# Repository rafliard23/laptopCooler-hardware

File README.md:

# laptopCooler-hardware

Hardware component of my custom laptop cooler project.

Using 3Pins PC Fans and speed controlled using 555 Timer and N-FET, powered with 12V Adapter (Ampere selection based on fan amp rating).

© 2022 Muhammad Rafli Ardiansyah

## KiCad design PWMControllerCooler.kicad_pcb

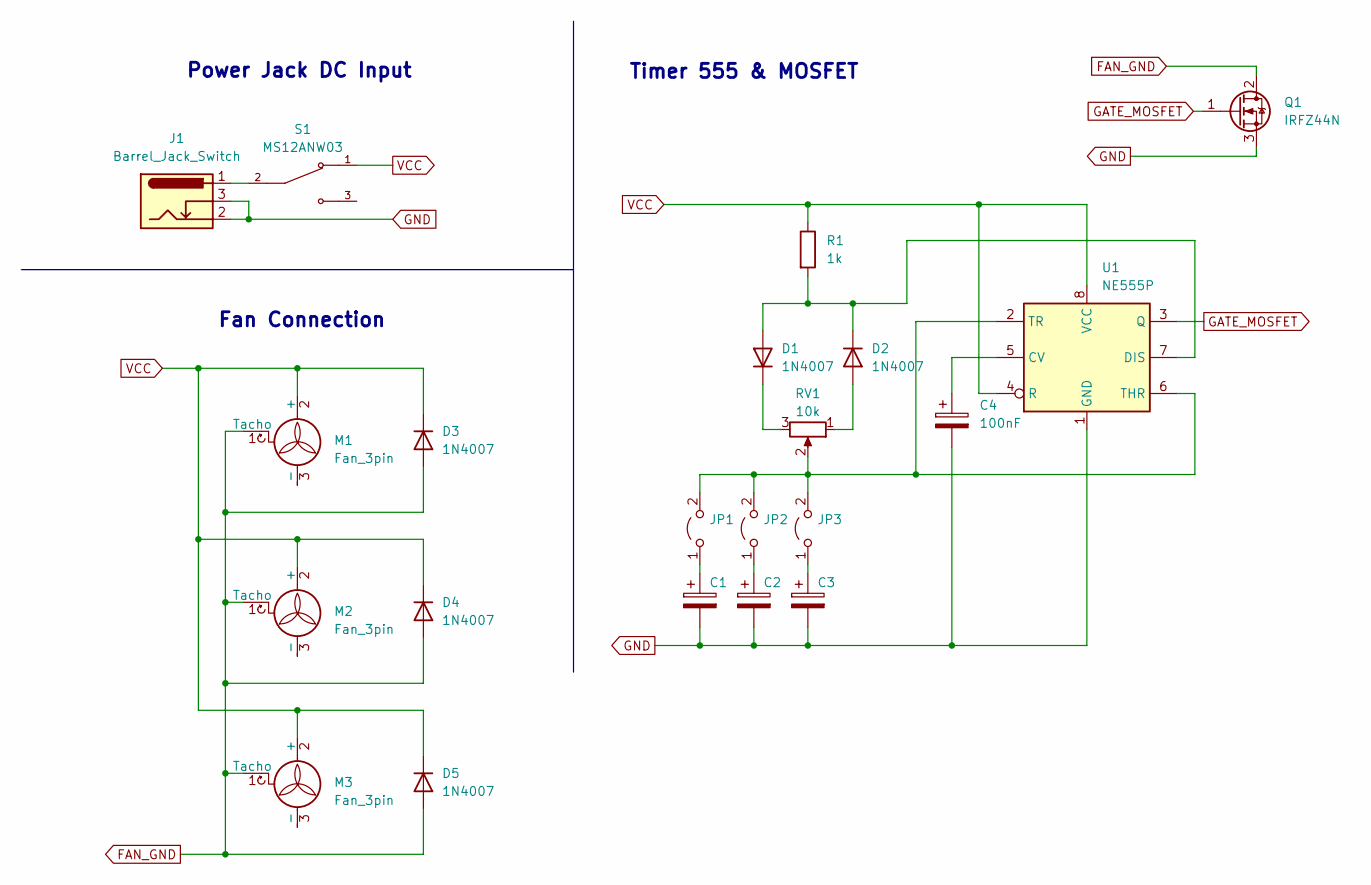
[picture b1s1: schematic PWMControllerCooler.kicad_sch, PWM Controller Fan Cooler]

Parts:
C1, C2, C3: C_Polarized; CP_Radial_D6.3mm_P2.50mm
C4: 100nF; CP_Radial_D8.0mm_P2.50mm
D1, D2, D3, D4, D5: 1N4007; D_DO-41_SOD81_P7.62mm_Horizontal
J1: Barrel_Jack_Switch; BarrelJack_Horizontal
JP1, JP2, JP3: Jumper_2_Open; PinHeader_1x02_P2.54mm_Vertical
M1, M2, M3: Fan_3pin; FanPinHeader_1x03_P2.54mm_Vertical
Q1: IRFZ44N; TO-220-3_Vertical
R1: 1k; R_Axial_DIN0207_L6.3mm_D2.5mm_P10.16mm_Horizontal
RV1: 10k; Potentiometer_Alps_RK163_Single_Horizontal
S1: MS12ANW03; SW_MS12ANW03
U1: NE555P; DIP-8_W7.62mm

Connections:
FAN_GND: D3.2 (A), D4.2 (A), D5.2 (A), M1.1 (Tacho), M2.1 (Tacho), M3.1 (Tacho), Q1.2 (D)
GATE_MOSFET: Q1.1 (G), U1.3 (Q)
GND: C1.2, C2.2, C3.2, C4.2, J1.2, J1.3, Q1.3 (S), U1.1 (GND)
unnamed: C1.1, JP1.1 (A)
unnamed: C2.1, JP2.1 (A)
unnamed: C3.1, JP3.1 (A)
unnamed: C4.1, U1.5 (CV)
unnamed: D1.1 (K), RV1.3
unnamed: D1.2 (A), D2.1 (K), R1.2, U1.7 (DIS)
unnamed: D2.2 (A), RV1.1
unnamed: JP1.2 (B), JP2.2 (B), JP3.2 (B), RV1.2, U1.2 (TR), U1.6 (THR)
unnamed: J1.1, S1.2
VCC: D3.1 (K), D4.1 (K), D5.1 (K), M1.2 (+), M2.2 (+), M3.2 (+), R1.1, S1.1, U1.4 (R), U1.8 (VCC)

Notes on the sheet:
Power Jack DC Input
Timer 555 & MOSFET
Fan Connection

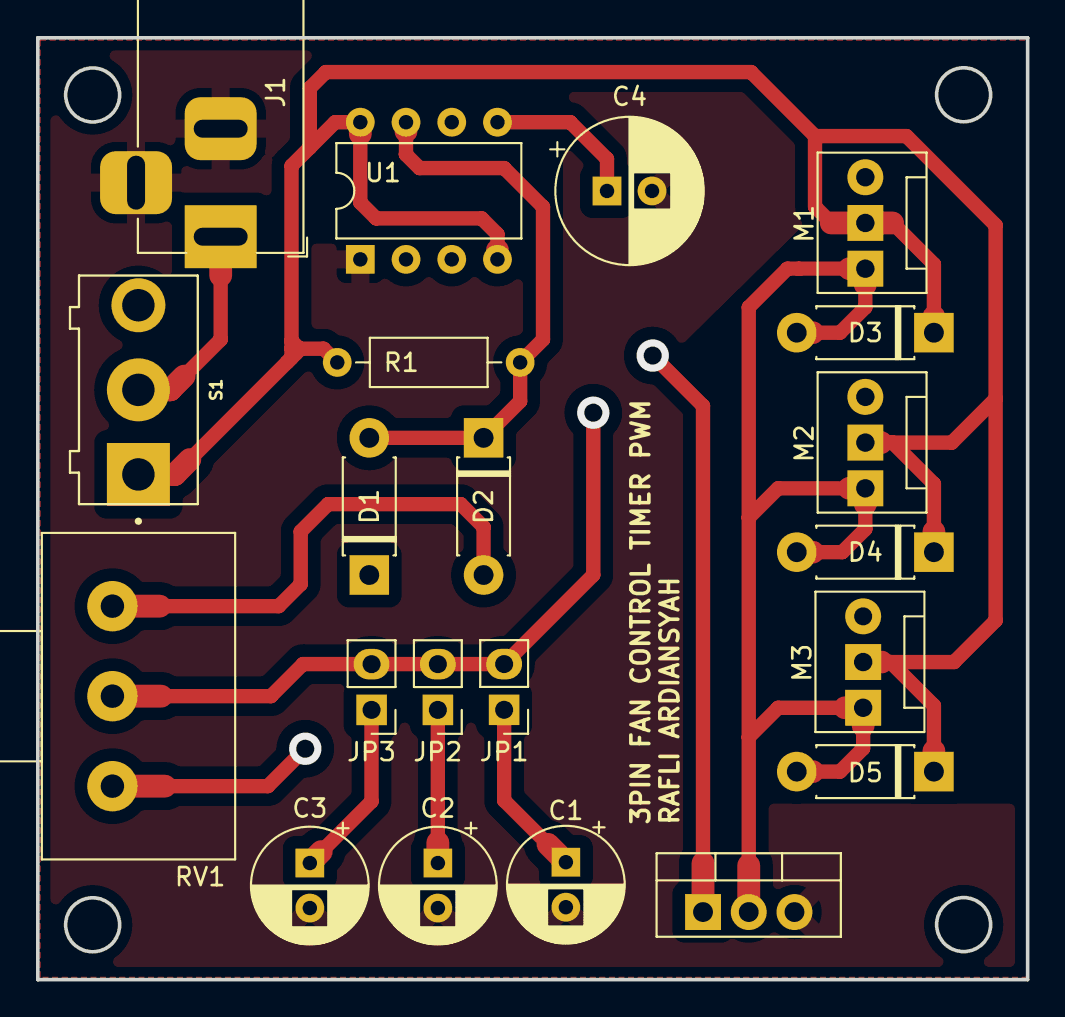
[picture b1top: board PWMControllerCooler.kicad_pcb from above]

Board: 2 copper layers, 55.0 x 52.3 mm, 21 parts (0 on the bottom side), 13 nets.

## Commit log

2023-10-18 Added files via upload
